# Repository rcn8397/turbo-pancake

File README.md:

# turbo-pancake
Simple breakout board for keeb'ing.

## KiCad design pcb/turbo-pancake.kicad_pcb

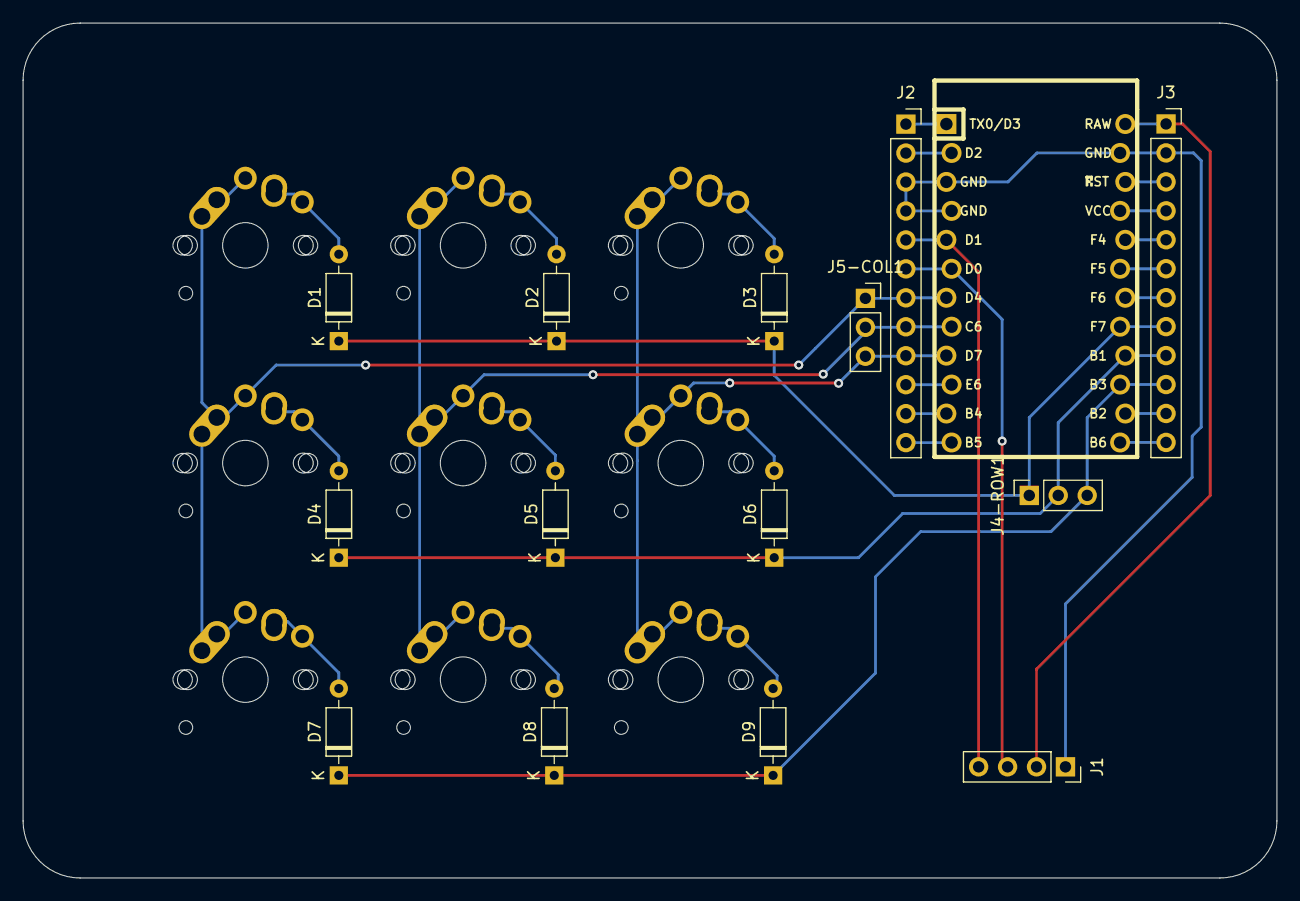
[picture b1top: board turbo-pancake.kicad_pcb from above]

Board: 2 copper layers, 110.0 x 75.0 mm, 24 parts (0 on the bottom side), 31 nets.

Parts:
D1, D2, D3, D4, D5, D6, D7, D8, D9: D_Small; D_DO-35_SOD27_P7.62mm_Horizontal
J1: Conn_01x04; PinSocket_1x04_P2.54mm_Vertical
J2, J3: Conn_01x12; PinSocket_1x12_P2.54mm_Vertical
J4-ROW1, J5-COL1: Conn_01x03; PinSocket_1x03_P2.54mm_Vertical
SW1, SW2, SW3, SW4, SW5, SW6, SW7, SW8, SW9: MX_LED; MX-Alps-Choc-1U-NoLED
U1: ProMicro; ArduinoProMicro-ZigZag

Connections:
A0-PF7-D18: D1.1, D2.1, D3.1, J3.8, J4-ROW1.1, U1.17
A1-PF6-D19: J3.7, U1.18
A2-PF5-D20: J3.6, U1.19
A3-PF4-D21: J3.5, U1.20
A6-D4-PD4: J2.7, J5-COL1.1, SW1.2, SW4.2, SW7.2, U1.7
A7-D6-PD7: J2.9, J5-COL1.3, SW3.2, SW6.2, SW9.2, U1.9
A8-D8-PB4: J2.11, U1.11
A9-D9-PB5: J2.12, U1.12
COL1: J2.8, J5-COL1.2, SW2.2, SW5.2, SW8.2, U1.8
D2-PD1-SDA: J1.4, J2.5, U1.5
D3-PD0-SCL: J1.3, J2.6, U1.6
D7-PE6: J2.10, U1.10
D10-PB6-A10: J3.12, U1.13
D14-PB3-MISO: D7.1, D8.1, D9.1, J3.10, J4-ROW1.3, U1.15
D15-PB1-SCLK: D4.1, D5.1, D6.1, J3.9, J4-ROW1.2, U1.16
D16-PB2-MOSI: J3.11, U1.14
GND: J1.1, J2.3, J2.4, J3.2, U1.3, U1.4, U1.23
unnamed: D1.2, SW1.1
unnamed: D2.2, SW2.1
unnamed: D3.2, SW3.1
unnamed: D4.2, SW4.1
unnamed: D5.2, SW5.1
unnamed: D6.2, SW6.1
unnamed: D7.2, SW7.1
unnamed: D8.2, SW8.1
unnamed: D9.2, SW9.1
RAW: J1.2, J3.1, U1.24
RST: J3.3, U1.22
RX-D0-PD2: J2.2, U1.2
TX-D1-PD3: J2.1, U1.1
VCC: J3.4, U1.21

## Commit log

2021-11-25 init pcb
2021-11-26 3x3 MX Macro Pad Using Pro Micro
2021-11-26 Adding tables
2021-11-26 pcb parts placed
2021-11-26 Adding keyboard layout
2021-11-26 creating space
2021-11-26 switch dxf
2021-11-26 wired up power traces are too small
2021-11-26 rewired
